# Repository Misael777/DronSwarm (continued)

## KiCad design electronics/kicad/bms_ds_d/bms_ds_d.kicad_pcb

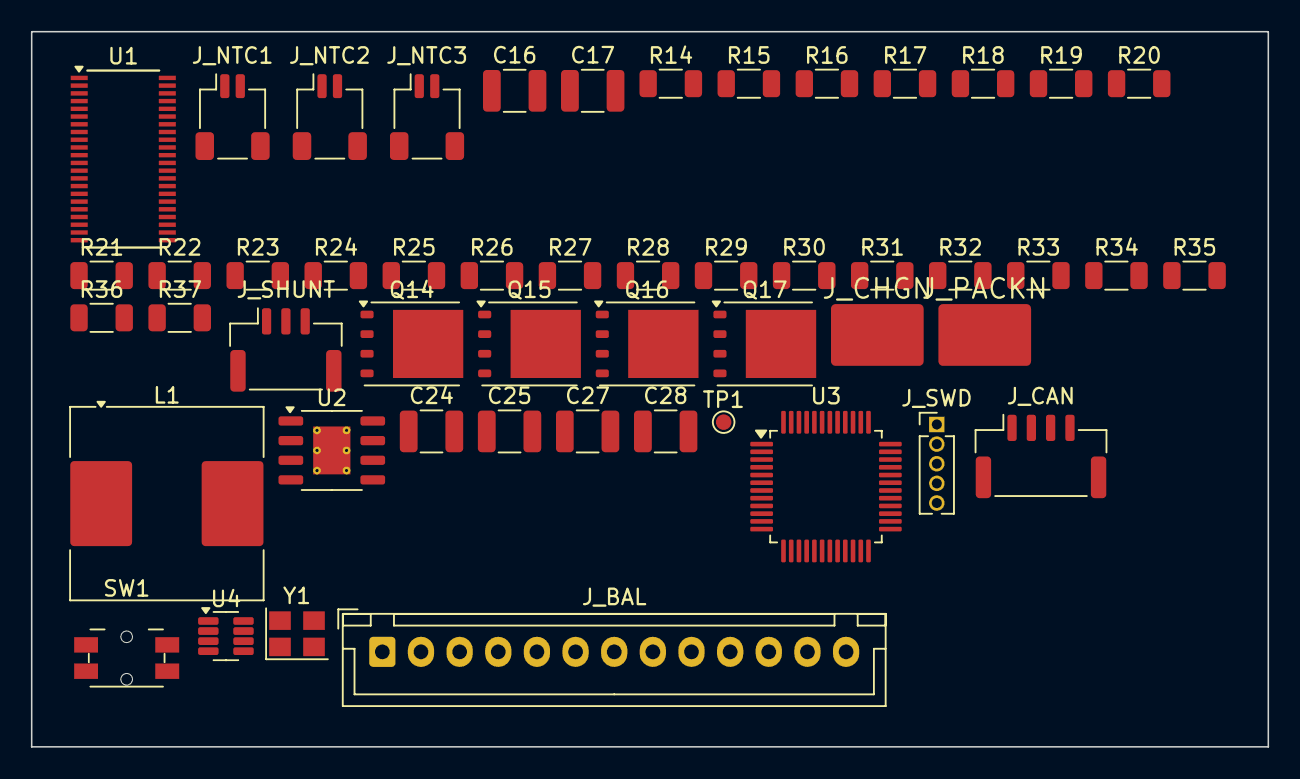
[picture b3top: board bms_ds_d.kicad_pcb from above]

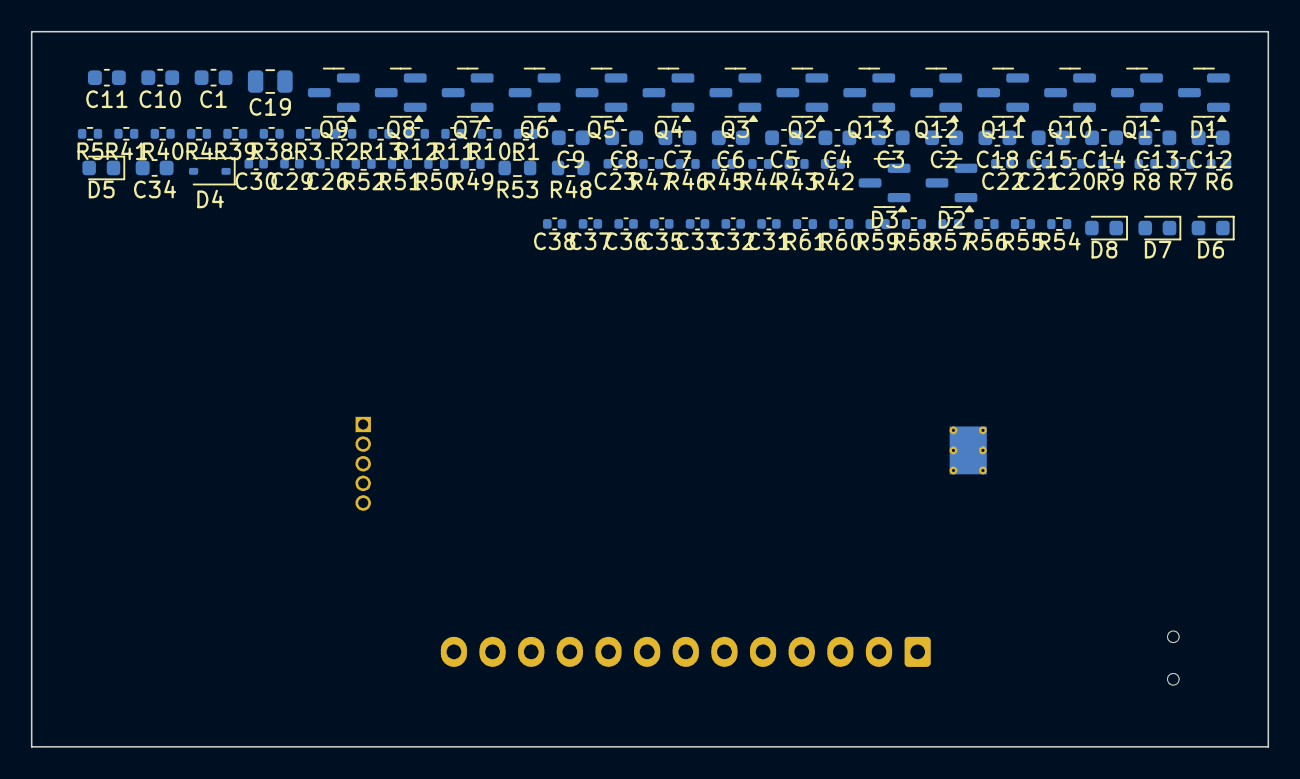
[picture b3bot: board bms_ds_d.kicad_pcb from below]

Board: 4 copper layers, 80.0 x 46.3 mm, 141 parts (90 on the bottom side), 104 nets, no tracks yet.

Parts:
C1, C2, C3, C4, C5, C6, C7, C8, C9, C10, C11, C12, C13, C14, C15: 1u/16V; C_0603_1608Metric
C16, C17: 4.7u/100V; C_1210_3225Metric
C18: 1u/25V; C_0603_1608Metric
C19: 4.7u/10V; C_0805_2012Metric
C20, C21, C22, C23, C31, C32, C33, C35, C38: 100n; C_0402_1005Metric
C24, C25: 2.2u/100V; C_1210_3225Metric
C26: 2.2n/50V; C_0402_1005Metric
C27, C28: 22u/10V; C_1210_3225Metric
C29: 3.3n; C_0402_1005Metric
C30: 150p/C0G; C_0402_1005Metric
C34: 4.7u; C_0603_1608Metric
C36, C37: 10p/C0G; C_0402_1005Metric
D1: BZX84C12; SOT-23
D2, D3: BZX84C15; SOT-23
D4: BAT54; D_SOD-323
D5, D6, D7, D8: verde; LED_0603_1608Metric
J_BAL: Conn_01x13; JST_XH_B13B-XH-A_1x13_P2.50mm_Vertical
J_CAN: Conn_01x04; JST_GH_SM04B-GHS-TB_1x04-1MP_P1.25mm_Horizontal
J_CHGN: Conn_01x01; Pad_Power_6x4mm
J_NTC1, J_NTC2, J_NTC3: Conn_01x02; JST_SH_SM02B-SRSS-TB_1x02-1MP_P1.00mm_Horizontal
J_PACKN: Conn_01x01; Pad_Power_6x4mm
J_SHUNT: Conn_01x03; JST_GH_SM03B-GHS-TB_1x03-1MP_P1.25mm_Horizontal
J_SWD: Conn_01x05; PinHeader_1x05_P1.27mm_Vertical
L1: 47u; L_Coilcraft_MSS1246-XXX
Q1, Q2, Q3, Q4, Q5, Q6, Q7, Q8, Q9, Q10, Q11, Q12: AO3401A; SOT-23
Q13: BSS123; SOT-23
Q14, Q15, Q16, Q17: BSC035N10NS5; TDSON-8-1
R1, R2, R3, R4, R5, R6, R7, R8, R9, R10, R11, R12, R13, R44, R46, R57, R58, R59, R60, R61: 1k; R_0402_1005Metric
R14, R15, R16, R17, R18, R19, R20, R21, R22, R23, R24, R25, R26, R27, R28, R29, R30, R31, R32, R33, R34, R35, R36, R37: 18; R_1206_3216Metric
R38, R39, R40, R42, R43: 100; R_0402_1005Metric
R41, R45, R47, R56: 1M; R_0402_1005Metric
R48: 1M; R_0603_1608Metric
R49: 45.3k; R_0402_1005Metric
R50: 27.4k; R_0402_1005Metric
R51: 174k; R_0402_1005Metric
R52: 100k; R_0402_1005Metric
R53: 140k; R_0603_1608Metric
R54, R55: 4.7k; R_0402_1005Metric
SW1: SW_Push; Panasonic_EVQPUL_EVQPUC
TP1: TestPoint; TestPoint_Pad_D1.0mm
U1: BQ7694003DBT; TSSOP-44_4.4x11.2mm_P0.5mm
U2: LM5164DDA; HSOP-8-1EP_3.9x4.9mm_P1.27mm_EP2.41x3.1mm_ThermalVias
U3: STM32G0B1CBTx; LQFP-48_7x7mm_P0.5mm
U4: TCAN330; SOT-23-8
Y1: 8MHz; Crystal_SMD_3225-4Pin_3.2x2.5mm

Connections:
3V3: C27.1, C28.1, C29.2, C31.1, C32.1, C33.1, C34.1, C38.1, J_SWD.1, L1.2, R51.1, R54.2, R55.2, U3.4, U3.5, U3.6, U4.3
5X_REF: C14.2, C21.2, J_NTC2.2, R38.2, U1.10
10X_REF: C15.2, C22.2, J_NTC3.2, R39.2, U1.15
AFE_ALERT: R56.1, U1.44, U3.44
AFE_BAT: C16.1, C17.1, Q13.3, R40.2, R41.1, U1.20
AFE_BOOT: D4.2, R57.2
BAL1_D: Q1.3, R14.1
BAL1_M: R14.2, R15.1
BAL2_D: Q2.3, R16.1
BAL2_M: R16.2, R17.1
BAL3_D: Q3.3, R18.1
BAL3_M: R18.2, R19.1
BAL4_D: Q4.3, R20.1
BAL4_M: R20.2, R21.1
BAL5_D: Q5.3, R22.1
BAL5_M: R22.2, R23.1
BAL6_D: Q6.3, R24.1
BAL6_M: R24.2, R25.1
BAL7_D: Q7.3, R26.1
BAL7_M: R26.2, R27.1
BAL8_D: Q8.3, R28.1
BAL8_M: R28.2, R29.1
BAL9_D: Q9.3, R30.1
BAL9_M: R30.2, R31.1
BAL10_D: Q10.3, R32.1
BAL10_M: R32.2, R33.1
BAL11_D: Q11.3, R34.1
BAL11_M: R34.2, R35.1
BAL12_D: Q12.3, R36.1
BAL12_M: R36.2, R37.1
BUCK_EN: R48.2, R49.1, U2.3
BUCK_FB: C30.2, R51.2, R52.1, U2.5
BUCK_RA: C29.1, C30.1, R53.2
CAP2: C14.1, U1.11, U1.12, U1.14
CAP3: C15.1, U1.16, U1.17, U1.19
CELL1: J_BAL.2, Q1.2, R2.1, R17.2
CELL2: J_BAL.3, Q2.2, R3.1, R19.2
CELL3: J_BAL.4, Q3.2, R4.1, R21.2
CELL4: J_BAL.5, Q4.2, R5.1, R23.2, R38.1
CELL5: J_BAL.6, Q5.2, R6.1, R25.2
CELL6: J_BAL.7, Q6.2, R7.1, R27.2
CELL7: J_BAL.8, Q7.2, R8.1, R29.2
CELL8: J_BAL.9, Q8.2, R9.1, R31.2, R39.1
CELL9: J_BAL.10, Q9.2, R10.1, R33.2
CELL10: J_BAL.11, Q10.2, R11.1, R35.2
CELL11: J_BAL.12, Q11.2, R12.1, R37.2
CELL12: C24.1, C25.1, J_BAL.13, Q12.2, R13.1, R40.1, R48.1, U2.2
CHG_G: D3.3, Q16.4, Q17.4, R46.2, R47.1
CHG_MID: Q14.5, Q15.5, Q16.5, Q17.5
CHG_N: D3.1, J_CHGN.1, Q16.1, Q16.2, Q16.3, Q17.1, Q17.2, Q17.3, R47.2
DSG_G: D2.3, Q14.4, Q15.4, R44.2, R45.1
GND: C13.2, C16.2, C17.2, C18.2, C19.2, C20.2, C24.2, C25.2, C27.2, C28.2, C31.2, C32.2, C33.2, C34.2, C35.2, C36.2, C37.2, C38.2, D1.1, D5.1, D6.1, D7.1, D8.1, J_BAL.1, J_CAN.4, J_NTC1.2, J_SHUNT.3, J_SWD.5, R1.1, R15.2, R49.2, R50.2, R52.2, R56.2, SW1.2, U1.3, U2.1, U2.9, U3.7, U4.2, U4.5, U4.8, Y1.2, Y1.4
unnamed: C13.1, U1.7
unnamed: C19.1, U1.8
unnamed: R44.1, U1.1
unnamed: R46.1, U1.2
unnamed: R50.1, U2.4
unnamed: C26.1, U2.7
unnamed: TP1.1, U2.6
unnamed: C36.1, U3.8, Y1.1
unnamed: C37.1, U3.9, Y1.3
unnamed: R54.1, U1.5, U3.45
unnamed: R55.1, U1.4, U3.46
unnamed: R57.1, U3.43
unnamed: U3.39, U4.1
unnamed: U3.38, U4.4
unnamed: J_CAN.2, U4.7
unnamed: J_CAN.3, U4.6
unnamed: R58.1, U3.19
unnamed: R59.1, U3.20
unnamed: R60.1, U3.21
unnamed: R61.1, U3.22
unnamed: SW1.1, U3.24
unnamed: J_SWD.2, U3.35
unnamed: J_SWD.3, U3.36
NRST: C35.1, J_SWD.4, U3.10
PACK_N: D2.1, J_PACKN.1, Q14.1, Q14.2, Q14.3, Q15.1, Q15.2, Q15.3, R45.2
REGSRC: C18.1, Q13.2, U1.9
REGSRC_G: D1.3, Q13.1, R41.2
SHUNT_K_N: J_SHUNT.2, R43.1
SHUNT_K_P: J_SHUNT.1, R42.1
SOC_LED1: D5.2, R58.2
SOC_LED2: D6.2, R59.2
SOC_LED3: D7.2, R60.2
SOC_LED4: D8.2, R61.2
SRN: C23.2, R43.2, U1.43
SRP: C23.1, R42.2, U1.42
SW_BUCK: C26.2, L1.1, R53.1, U2.8
TS1: C20.1, D4.1, J_NTC1.1, U1.6
TS2: C21.1, J_NTC2.1, U1.13
TS3: C22.1, J_NTC3.1, U1.18
VC_N0: C1.2, R1.2, U1.41
VC_N1: C1.1, C2.2, Q1.1, R2.2, U1.40
VC_N2: C2.1, C3.2, Q2.1, R3.2, U1.39
VC_N3: C3.1, C4.2, Q3.1, R4.2, U1.37, U1.38
VC_N4: C4.1, C5.2, Q4.1, R5.2, U1.35, U1.36
VC_N5: C5.1, C6.2, Q5.1, R6.2, U1.34
VC_N6: C6.1, C7.2, Q6.1, R7.2, U1.33
VC_N7: C7.1, C8.2, Q7.1, R8.2, U1.31, U1.32
VC_N8: C8.1, C9.2, Q8.1, R9.2, U1.29, U1.30
VC_N9: C9.1, C10.2, Q9.1, R10.2, U1.28
VC_N10: C10.1, C11.2, Q10.1, R11.2, U1.27
VC_N11: C11.1, C12.2, Q11.1, R12.2, U1.25, U1.26
VC_N12: C12.1, Q12.1, R13.2, U1.24

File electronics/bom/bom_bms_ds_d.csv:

Comment,Designator,Footprint,Quantity,Unit price USD (est.)
18,"R14,R15,R16,R17,R18,R19,R20,R21,R22,R23,R24,R25,R26,R27,R28,R29,R30,R31,R32,R33,R34,R35,R36,R37",Resistor_SMD:R_1206_3216Metric,24,0.008
1k,"R1,R2,R3,R4,R5,R6,R7,R8,R9,R10,R11,R12,R13,R44,R46,R57,R58,R59,R60,R61",Resistor_SMD:R_0402_1005Metric,20,0.002
1u/16V,"C1,C2,C3,C4,C5,C6,C7,C8,C9,C10,C11,C12,C13,C14,C15",Capacitor_SMD:C_0603_1608Metric,15,0.008
AO3401A,"Q1,Q2,Q3,Q4,Q5,Q6,Q7,Q8,Q9,Q10,Q11,Q12",Package_TO_SOT_SMD:SOT-23,12,0.03
100n,"C20,C21,C22,C23,C31,C32,C33,C35,C38",Capacitor_SMD:C_0402_1005Metric,9,0.004
100,"R38,R39,R40,R42,R43",Resistor_SMD:R_0402_1005Metric,5,0.002
1M,"R41,R45,R47,R56",Resistor_SMD:R_0402_1005Metric,4,0.002
BSC035N10NS5,"Q14,Q15,Q16,Q17",Package_TO_SOT_SMD:TDSON-8-1,4,1.2
verde,"D5,D6,D7,D8",LED_SMD:LED_0603_1608Metric,4,0.02
Conn_01x02,"J_NTC1,J_NTC2,J_NTC3",Connector_JST:JST_SH_SM02B-SRSS-TB_1x02-1MP_P1.00mm_Horizontal,3,0.12
10p/C0G,"C36,C37",Capacitor_SMD:C_0402_1005Metric,2,0.004
2.2u/100V,"C24,C25",Capacitor_SMD:C_1210_3225Metric,2,0.15
22u/10V,"C27,C28",Capacitor_SMD:C_1210_3225Metric,2,0.1
4.7k,"R54,R55",Resistor_SMD:R_0402_1005Metric,2,0.002
4.7u/100V,"C16,C17",Capacitor_SMD:C_1210_3225Metric,2,0.25
BZX84C15,"D2,D3",Package_TO_SOT_SMD:SOT-23,2,0.02
Conn_01x01,"J_CHGN,J_PACKN",DronSwarm:Pad_Power_6x4mm,2,0.0
100k,R52,Resistor_SMD:R_0402_1005Metric,1,0.002
140k,R53,Resistor_SMD:R_0603_1608Metric,1,0.003
150p/C0G,C30,Capacitor_SMD:C_0402_1005Metric,1,0.004
174k,R51,Resistor_SMD:R_0402_1005Metric,1,0.002
1M,R48,Resistor_SMD:R_0603_1608Metric,1,0.003
1u/25V,C18,Capacitor_SMD:C_0603_1608Metric,1,0.008
2.2n/50V,C26,Capacitor_SMD:C_0402_1005Metric,1,0.004
27.4k,R50,Resistor_SMD:R_0402_1005Metric,1,0.002
3.3n,C29,Capacitor_SMD:C_0402_1005Metric,1,0.004
4.7u,C34,Capacitor_SMD:C_0603_1608Metric,1,0.008
4.7u/10V,C19,Capacitor_SMD:C_0805_2012Metric,1,0.03
45.3k,R49,Resistor_SMD:R_0402_1005Metric,1,0.002
47u,L1,Inductor_SMD:L_Coilcraft_MSS1246-XXX,1,0.45
8MHz,Y1,Crystal:Crystal_SMD_3225-4Pin_3.2x2.5mm,1,0.12
BAT54,D4,Diode_SMD:D_SOD-323,1,0.03
BQ7694003DBT,U1,Package_SO:TSSOP-44_4.4x11.2mm_P0.5mm,1,3.0
BSS123,Q13,Package_TO_SOT_SMD:SOT-23,1,0.02
BZX84C12,D1,Package_TO_SOT_SMD:SOT-23,1,0.02
Conn_01x03,J_SHUNT,Connector_JST:JST_GH_SM03B-GHS-TB_1x03-1MP_P1.25mm_Horizontal,1,0.18
Conn_01x04,J_CAN,Connector_JST:JST_GH_SM04B-GHS-TB_1x04-1MP_P1.25mm_Horizontal,1,0.2
Conn_01x05,J_SWD,Connector_PinHeader_1.27mm:PinHeader_1x05_P1.27mm_Vertical,1,0.05
Conn_01x13,J_BAL,Connector_JST:JST_XH_B13B-XH-A_1x13_P2.50mm_Vertical,1,0.25
LM5164DDA,U2,Package_SO:HSOP-8-1EP_3.9x4.9mm_P1.27mm_EP2.41x3.1mm_ThermalVias,1,1.4
STM32G0B1CBTx,U3,Package_QFP:LQFP-48_7x7mm_P0.5mm,1,2.2
SW_Push,SW1,Button_Switch_SMD:Panasonic_EVQPUL_EVQPUC,1,0.1
TCAN330,U4,Package_TO_SOT_SMD:SOT-23-8,1,0.9
TestPoint,TP1,TestPoint:TestPoint_Pad_D1.0mm,1,0.0

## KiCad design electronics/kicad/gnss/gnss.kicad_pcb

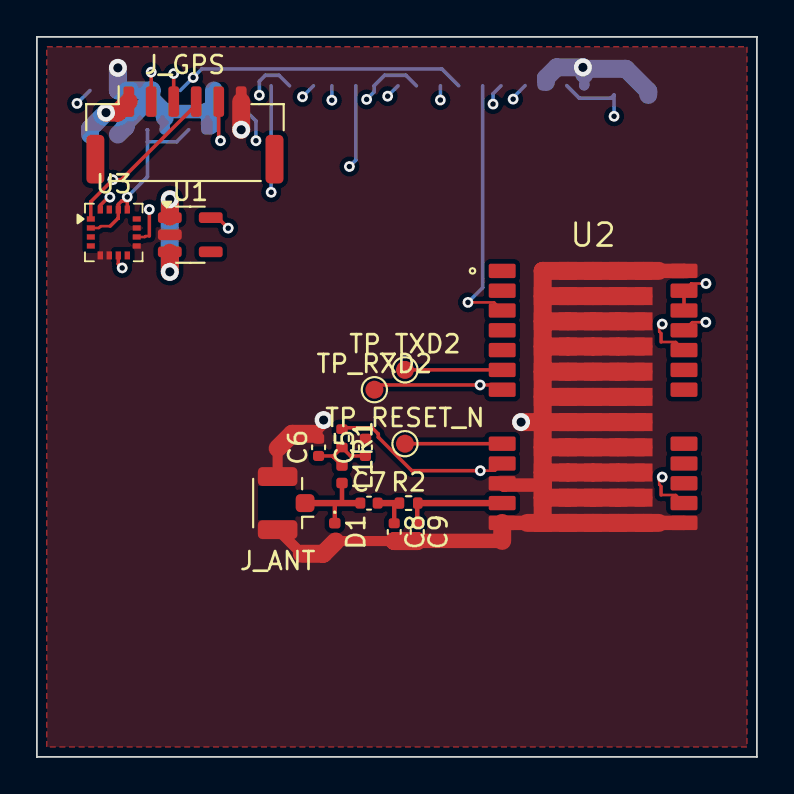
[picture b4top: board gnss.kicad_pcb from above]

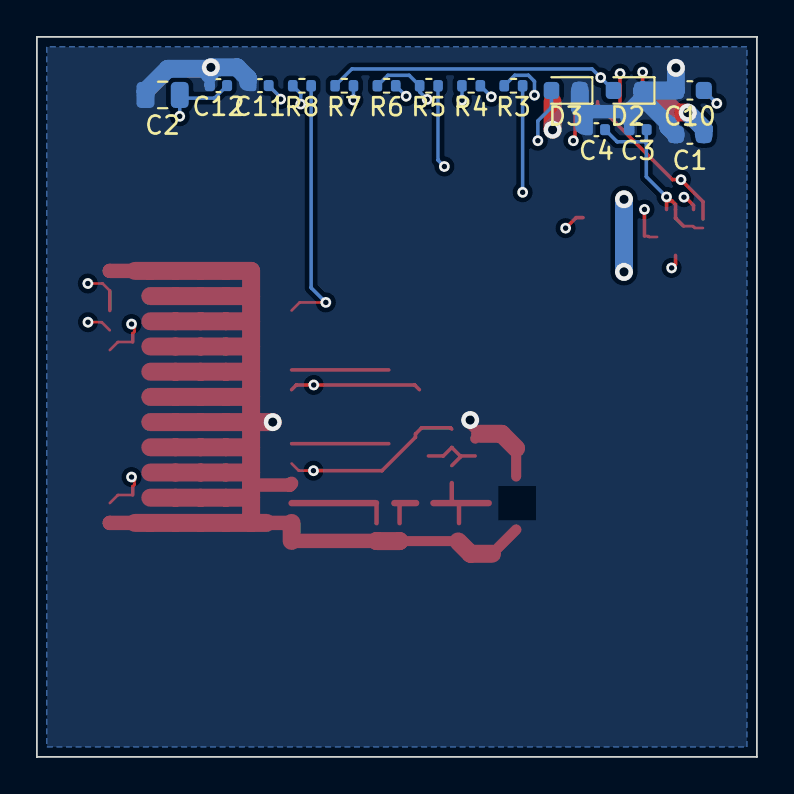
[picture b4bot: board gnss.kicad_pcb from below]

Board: 4 copper layers, 40.0 x 40.0 mm, 32 parts (15 on the bottom side), 23 nets.

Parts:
C1, C10: 1u; C_0603_1608Metric
C2: 10u/10V; C_0805_2012Metric
C3, C6, C11, C12: 100n; C_0402_1005Metric
C4, C5, C7: 100p/C0G; C_0402_1005Metric
C8, C9: DNP; C_0402_1005Metric
D1: ESD0P2RF-02LS; D_0402_1005Metric
D2: verde; LED_0603_1608Metric
D3: azul; LED_0603_1608Metric
J_ANT: Conn_Coaxial; U.FL_Hirose_U.FL-R-SMT-1_Vertical
J_GPS: Conn_01x06; JST_GH_SM06B-GHS-TB_1x06-1MP_P1.25mm_Horizontal
L1: 68n; L_0402_1005Metric
R1: 10; R_0402_1005Metric
R2: 0; R_0402_1005Metric
R3, R4: 22; R_0402_1005Metric
R5, R6: 2.2k; R_0402_1005Metric
R7, R8: 1k; R_0402_1005Metric
TP_RESET_N: TestPoint; TestPoint_Pad_D1.0mm
TP_RXD2: TestPoint; TestPoint_Pad_D1.0mm
TP_TXD2: TestPoint; TestPoint_Pad_D1.0mm
U1: TLV75533PDBV; SOT-23-5
U2: LG290P; Quectel_LG290P_LGA-79_12.2x16mm
U3: IST8310; LGA-16_3x3mm_P0.5mm

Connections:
3V3_GNSS: C2.1, C3.1, C4.1, C12.1, R5.2, R6.2, U1.5, U2.22, U2.23, U3.2, U3.13, U3.14
5V: C1.1, J_GPS.1, U1.1, U1.3
ANT_FEED: C5.1, C6.1, L1.1, R1.2
ANT_LINE: C7.1, D1.1, J_ANT.1, L1.2
GND: C1.2, C2.2, C3.2, C4.2, C5.2, C6.2, C8.2, C9.2, C10.2, C11.2, C12.2, D1.2, D2.1, D3.1, J_ANT.2, J_GPS.6, U1.2, U2.10, U2.12, U2.13, U2.24, U2.25, U2.26, U2.27, U2.28, U2.29, U2.30, U2.31, U2.32, U2.33, U2.34, U2.35, U2.36, U2.37, U2.38, U2.39, U2.40, U2.41, U2.42, U2.43, U2.44, U2.45, U2.46, U2.47, U2.48, U2.49, U2.50, U2.51, U2.52, U2.53, U2.54, U2.55, U2.56, U2.57, U2.58, U2.59, U2.60, U2.61, U2.62, U2.63, U2.64, U2.65, U2.66, U2.67, U2.68, U2.69, U2.70, U2.71, U2.72, U2.73, U2.74, U2.75, U2.76, U2.77, U2.78, U2.79, U3.5, U3.6, U3.9, U3.11
GPS_RX: J_GPS.2, R4.1
GPS_TX: J_GPS.3, R3.2
I2C_SCL: J_GPS.4, R5.1, U3.1
I2C_SDA: J_GPS.5, R6.1, U3.16
LED_1PPS: D3.2, R8.2
LED_RTK_STAT: D2.2, R7.2
unnamed: R3.1, U2.20
unnamed: R4.2, U2.21
unnamed: C10.1, U3.10
unnamed: C11.1, U3.7
unnamed: R7.1, U2.14
unnamed: R8.1, U2.3
unnamed: TP_TXD2.1, U2.6
unnamed: TP_RXD2.1, U2.7
unnamed: TP_RESET_N.1, U2.8
RF_IN: C9.1, R2.2, U2.11
RF_PI: C7.2, C8.1, R2.1
VDD_RF: R1.1, U2.9

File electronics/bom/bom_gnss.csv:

Comment,Designator,Footprint,Quantity,Unit price USD (est.)
100n,"C3,C6,C11,C12",Capacitor_SMD:C_0402_1005Metric,4,0.004
100p/C0G,"C4,C5,C7",Capacitor_SMD:C_0402_1005Metric,3,0.004
TestPoint,"TP_RESET_N,TP_RXD2,TP_TXD2",TestPoint:TestPoint_Pad_D1.0mm,3,0.0
1k,"R7,R8",Resistor_SMD:R_0402_1005Metric,2,0.002
1u,"C1,C10",Capacitor_SMD:C_0603_1608Metric,2,0.008
2.2k,"R5,R6",Resistor_SMD:R_0402_1005Metric,2,0.002
22,"R3,R4",Resistor_SMD:R_0402_1005Metric,2,0.002
DNP,"C8,C9",Capacitor_SMD:C_0402_1005Metric,2,0.004
0,R2,Resistor_SMD:R_0402_1005Metric,1,0.002
10,R1,Resistor_SMD:R_0402_1005Metric,1,0.002
10u/10V,C2,Capacitor_SMD:C_0805_2012Metric,1,0.03
68n,L1,Inductor_SMD:L_0402_1005Metric,1,0.02
Conn_01x06,J_GPS,Connector_JST:JST_GH_SM06B-GHS-TB_1x06-1MP_P1.25mm_Horizontal,1,0.24
Conn_Coaxial,J_ANT,Connector_Coaxial:U.FL_Hirose_U.FL-R-SMT-1_Vertical,1,0.2
ESD0P2RF-02LS,D1,Diode_SMD:D_0402_1005Metric,1,0.1
IST8310,U3,Package_LGA:LGA-16_3x3mm_P0.5mm,1,0.8
LG290P,U2,DronSwarm:Quectel_LG290P_LGA-79_12.2x16mm,1,72.0
TLV75533PDBV,U1,Package_TO_SOT_SMD:SOT-23-5,1,0.12
azul,D3,LED_SMD:LED_0603_1608Metric,1,0.02
verde,D2,LED_SMD:LED_0603_1608Metric,1,0.02

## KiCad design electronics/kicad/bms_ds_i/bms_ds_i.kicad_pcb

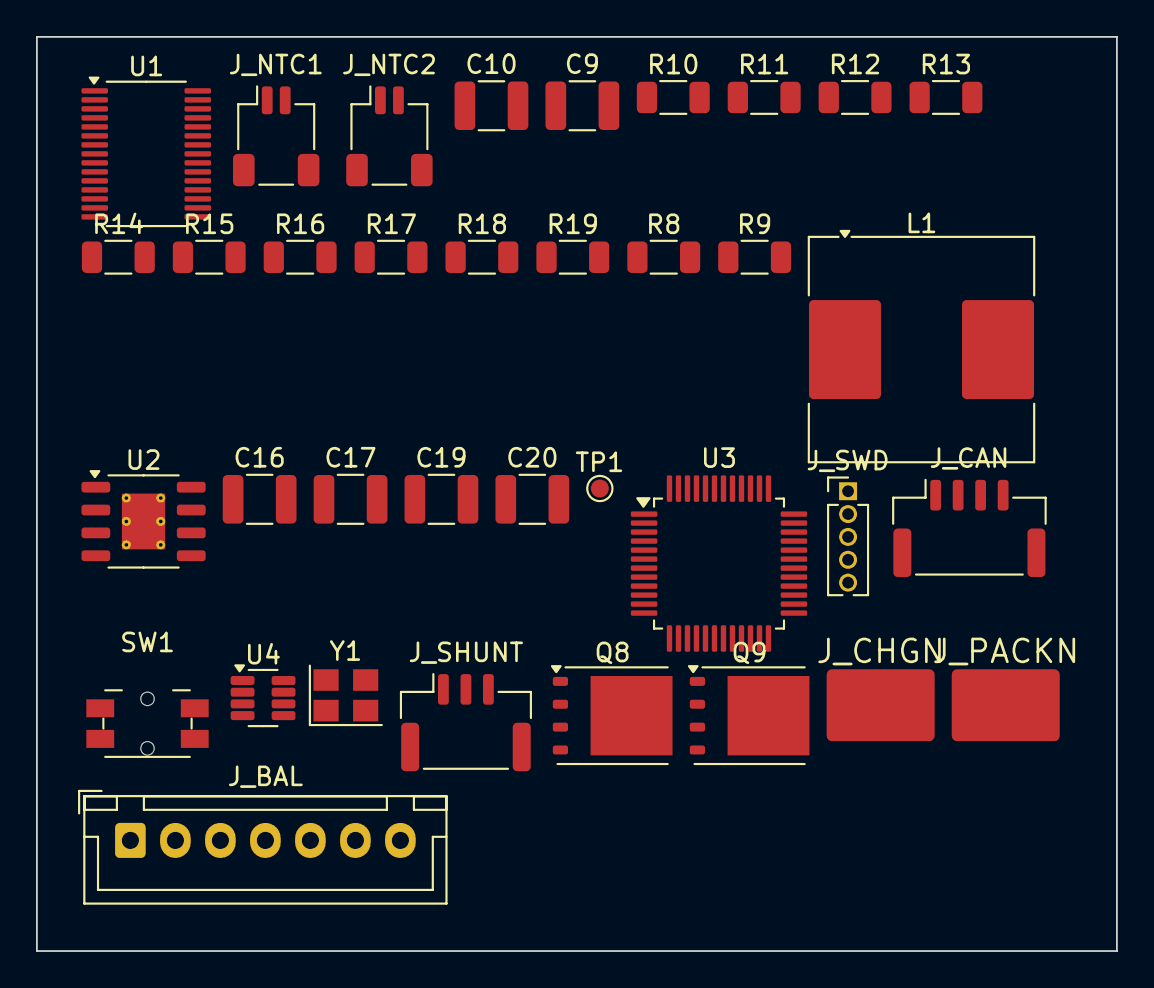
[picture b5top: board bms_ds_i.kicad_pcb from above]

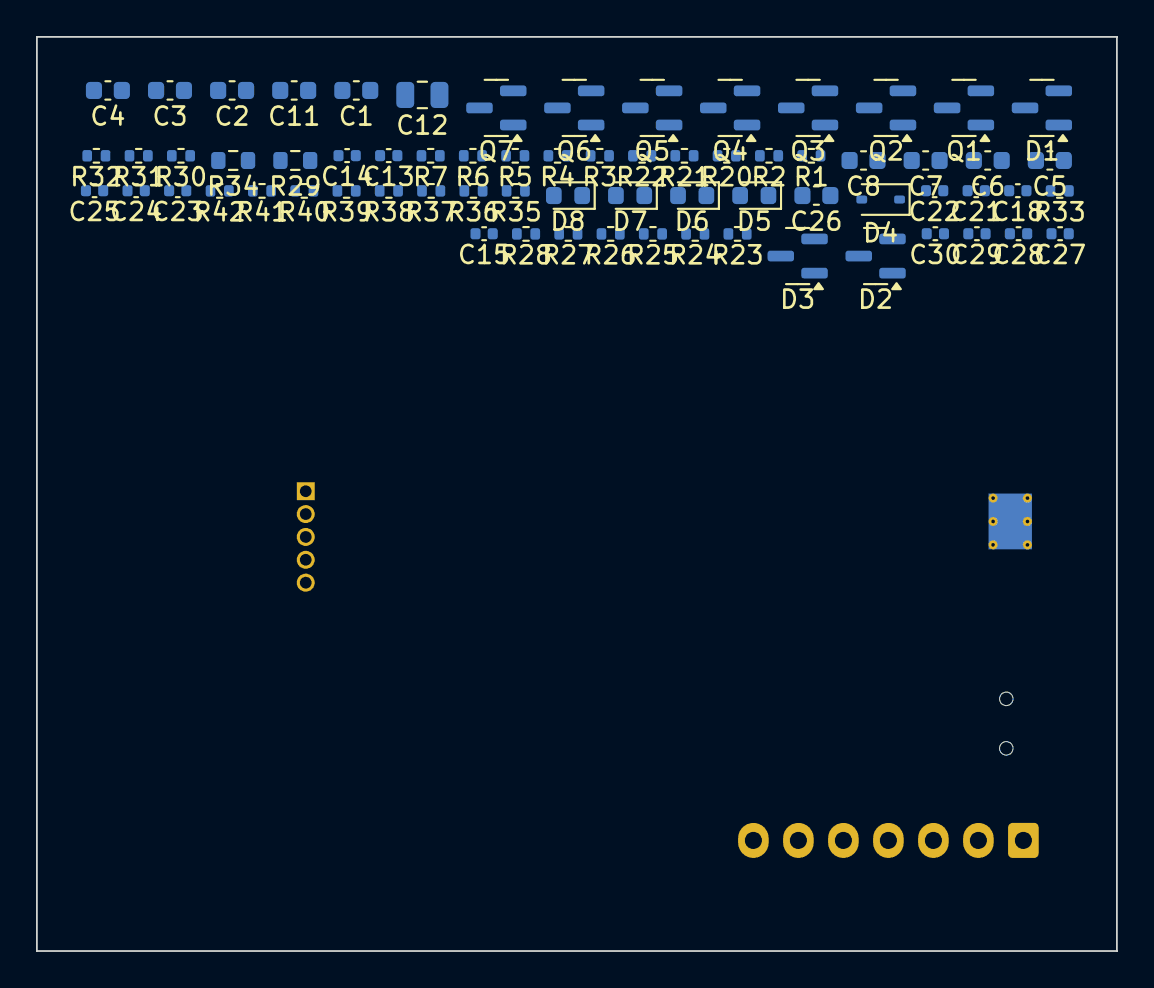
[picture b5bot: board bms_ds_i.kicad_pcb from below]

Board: 4 copper layers, 60.0 x 50.8 mm, 105 parts (69 on the bottom side), 77 nets, no tracks yet.

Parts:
C1, C2, C3, C4, C5, C6, C7, C8: 1u/16V; C_0603_1608Metric
C9, C10: 4.7u/100V; C_1210_3225Metric
C11: 1u/25V; C_0603_1608Metric
C12: 4.7u/10V; C_0805_2012Metric
C13, C14, C15, C23, C24, C25, C27, C30: 100n; C_0402_1005Metric
C16, C17: 2.2u/100V; C_1210_3225Metric
C18: 2.2n/50V; C_0402_1005Metric
C19, C20: 22u/10V; C_1210_3225Metric
C21: 3.3n; C_0402_1005Metric
C22: 150p/C0G; C_0402_1005Metric
C26: 4.7u; C_0603_1608Metric
C28, C29: 10p/C0G; C_0402_1005Metric
D1: BZX84C12; SOT-23
D2, D3: BZX84C15; SOT-23
D4: BAT54; D_SOD-323
D5, D6, D7, D8: verde; LED_0603_1608Metric
J_BAL: Conn_01x07; JST_XH_B7B-XH-A_1x07_P2.50mm_Vertical
J_CAN: Conn_01x04; JST_GH_SM04B-GHS-TB_1x04-1MP_P1.25mm_Horizontal
J_CHGN: Conn_01x01; Pad_Power_6x4mm
J_NTC1, J_NTC2: Conn_01x02; JST_SH_SM02B-SRSS-TB_1x02-1MP_P1.00mm_Horizontal
J_PACKN: Conn_01x01; Pad_Power_6x4mm
J_SHUNT: Conn_01x03; JST_GH_SM03B-GHS-TB_1x03-1MP_P1.25mm_Horizontal
J_SWD: Conn_01x05; PinHeader_1x05_P1.27mm_Vertical
L1: 47u; L_Coilcraft_MSS1246-XXX
Q1, Q2, Q3, Q4, Q5, Q6: AO3401A; SOT-23
Q7: BSS123; SOT-23
Q8, Q9: BSC035N10NS5; TDSON-8-1
R1, R2, R3, R4, R5, R6, R7, R25, R27, R38, R39, R40, R41, R42: 1k; R_0402_1005Metric
R8, R9, R10, R11, R12, R13, R14, R15, R16, R17, R18, R19: 18; R_1206_3216Metric
R20, R21, R23, R24: 100; R_0402_1005Metric
R22, R26, R28, R37: 1M; R_0402_1005Metric
R29: 1M; R_0603_1608Metric
R30: 94.2k; R_0402_1005Metric
R31: 27.4k; R_0402_1005Metric
R32: 174k; R_0402_1005Metric
R33: 100k; R_0402_1005Metric
R34: 140k; R_0603_1608Metric
R35, R36: 4.7k; R_0402_1005Metric
SW1: SW_Push; Panasonic_EVQPUL_EVQPUC
TP1: TestPoint; TestPoint_Pad_D1.0mm
U1: BQ7693003DBT; TSSOP-30_4.4x7.8mm_P0.5mm
U2: LM5164DDA; HSOP-8-1EP_3.9x4.9mm_P1.27mm_EP2.41x3.1mm_ThermalVias
U3: STM32G0B1CBTx; LQFP-48_7x7mm_P0.5mm
U4: TCAN330; SOT-23-8
Y1: 8MHz; Crystal_SMD_3225-4Pin_3.2x2.5mm

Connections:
3V3: C19.1, C20.1, C21.2, C23.1, C24.1, C25.1, C26.1, C30.1, J_SWD.1, L1.2, R32.1, R35.2, R36.2, U3.4, U3.5, U3.6, U4.3
5X_REF: C8.2, C14.2, J_NTC2.2, R20.2, U1.10
AFE_ALERT: R37.1, U1.30, U3.44
AFE_BAT: C9.1, C10.1, Q7.3, R21.2, R22.1, U1.15
AFE_BOOT: D4.2, R38.2
BAL1_D: Q1.3, R8.1
BAL1_M: R8.2, R9.1
BAL2_D: Q2.3, R10.1
BAL2_M: R10.2, R11.1
BAL3_D: Q3.3, R12.1
BAL3_M: R12.2, R13.1
BAL4_D: Q4.3, R14.1
BAL4_M: R14.2, R15.1
BAL5_D: Q5.3, R16.1
BAL5_M: R16.2, R17.1
BAL6_D: Q6.3, R18.1
BAL6_M: R18.2, R19.1
BUCK_EN: R29.2, R30.1, U2.3
BUCK_FB: C22.2, R32.2, R33.1, U2.5
BUCK_RA: C21.1, C22.1, R34.2
CAP2: C8.1, U1.11, U1.12, U1.14
CELL1: J_BAL.2, Q1.2, R2.1, R11.2
CELL2: J_BAL.3, Q2.2, R3.1, R13.2
CELL3: J_BAL.4, Q3.2, R4.1, R15.2, R20.1
CELL4: J_BAL.5, Q4.2, R5.1, R17.2
CELL5: J_BAL.6, Q5.2, R6.1, R19.2
CELL6: C16.1, C17.1, J_BAL.7, Q6.2, R7.1, R21.1, R29.1, U2.2
CHG_G: D3.3, Q9.4, R27.2, R28.1
CHG_MID: Q8.5, Q9.5
CHG_N: D3.1, J_CHGN.1, Q9.1, Q9.2, Q9.3, R28.2
DSG_G: D2.3, Q8.4, R25.2, R26.1
GND: C7.2, C9.2, C10.2, C11.2, C12.2, C13.2, C16.2, C17.2, C19.2, C20.2, C23.2, C24.2, C25.2, C26.2, C27.2, C28.2, C29.2, C30.2, D1.1, D5.1, D6.1, D7.1, D8.1, J_BAL.1, J_CAN.4, J_NTC1.2, J_SHUNT.3, J_SWD.5, R1.1, R9.2, R30.2, R31.2, R33.2, R37.2, SW1.2, U1.3, U2.1, U2.9, U3.7, U4.2, U4.5, U4.8, Y1.2, Y1.4
unnamed: C7.1, U1.7
unnamed: C12.1, U1.8
unnamed: R25.1, U1.1
unnamed: R27.1, U1.2
unnamed: R31.1, U2.4
unnamed: C18.1, U2.7
unnamed: TP1.1, U2.6
unnamed: C28.1, U3.8, Y1.1
unnamed: C29.1, U3.9, Y1.3
unnamed: R35.1, U1.5, U3.45
unnamed: R36.1, U1.4, U3.46
unnamed: R38.1, U3.43
unnamed: U3.39, U4.1
unnamed: U3.38, U4.4
unnamed: J_CAN.2, U4.7
unnamed: J_CAN.3, U4.6
unnamed: R39.1, U3.19
unnamed: R40.1, U3.20
unnamed: R41.1, U3.21
unnamed: R42.1, U3.22
unnamed: SW1.1, U3.24
unnamed: J_SWD.2, U3.35
unnamed: J_SWD.3, U3.36
NRST: C27.1, J_SWD.4, U3.10
PACK_N: D2.1, J_PACKN.1, Q8.1, Q8.2, Q8.3, R26.2
REGSRC: C11.1, Q7.2, U1.9
REGSRC_G: D1.3, Q7.1, R22.2
SHUNT_K_N: J_SHUNT.2, R24.1
SHUNT_K_P: J_SHUNT.1, R23.1
SOC_LED1: D5.2, R39.2
SOC_LED2: D6.2, R40.2
SOC_LED3: D7.2, R41.2
SOC_LED4: D8.2, R42.2
SRN: C15.2, R24.2, U1.29
SRP: C15.1, R23.2, U1.28
SW_BUCK: C18.2, L1.1, R34.1, U2.8
TS1: C13.1, D4.1, J_NTC1.1, U1.6
TS2: C14.1, J_NTC2.1, U1.13
VC_N0: C1.2, R1.2, U1.27
VC_N1: C1.1, C2.2, Q1.1, R2.2, U1.26
VC_N2: C2.1, C3.2, Q2.1, R3.2, U1.23, U1.24, U1.25
VC_N3: C3.1, C4.2, Q3.1, R4.2, U1.21, U1.22
VC_N4: C4.1, C5.2, Q4.1, R5.2, U1.20
VC_N5: C5.1, C6.2, Q5.1, R6.2, U1.17, U1.18, U1.19
VC_N6: C6.1, Q6.1, R7.2, U1.16

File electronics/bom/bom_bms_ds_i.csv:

Comment,Designator,Footprint,Quantity,Unit price USD (est.)
1k,"R1,R2,R3,R4,R5,R6,R7,R25,R27,R38,R39,R40,R41,R42",Resistor_SMD:R_0402_1005Metric,14,0.002
18,"R8,R9,R10,R11,R12,R13,R14,R15,R16,R17,R18,R19",Resistor_SMD:R_1206_3216Metric,12,0.008
100n,"C13,C14,C15,C23,C24,C25,C27,C30",Capacitor_SMD:C_0402_1005Metric,8,0.004
1u/16V,"C1,C2,C3,C4,C5,C6,C7,C8",Capacitor_SMD:C_0603_1608Metric,8,0.008
AO3401A,"Q1,Q2,Q3,Q4,Q5,Q6",Package_TO_SOT_SMD:SOT-23,6,0.03
100,"R20,R21,R23,R24",Resistor_SMD:R_0402_1005Metric,4,0.002
1M,"R22,R26,R28,R37",Resistor_SMD:R_0402_1005Metric,4,0.002
verde,"D5,D6,D7,D8",LED_SMD:LED_0603_1608Metric,4,0.02
10p/C0G,"C28,C29",Capacitor_SMD:C_0402_1005Metric,2,0.004
2.2u/100V,"C16,C17",Capacitor_SMD:C_1210_3225Metric,2,0.15
22u/10V,"C19,C20",Capacitor_SMD:C_1210_3225Metric,2,0.1
4.7k,"R35,R36",Resistor_SMD:R_0402_1005Metric,2,0.002
4.7u/100V,"C9,C10",Capacitor_SMD:C_1210_3225Metric,2,0.25
BSC035N10NS5,"Q8,Q9",Package_TO_SOT_SMD:TDSON-8-1,2,1.2
BZX84C15,"D2,D3",Package_TO_SOT_SMD:SOT-23,2,0.02
Conn_01x01,"J_CHGN,J_PACKN",DronSwarm:Pad_Power_6x4mm,2,0.0
Conn_01x02,"J_NTC1,J_NTC2",Connector_JST:JST_SH_SM02B-SRSS-TB_1x02-1MP_P1.00mm_Horizontal,2,0.12
100k,R33,Resistor_SMD:R_0402_1005Metric,1,0.002
140k,R34,Resistor_SMD:R_0603_1608Metric,1,0.003
150p/C0G,C22,Capacitor_SMD:C_0402_1005Metric,1,0.004
174k,R32,Resistor_SMD:R_0402_1005Metric,1,0.002
1M,R29,Resistor_SMD:R_0603_1608Metric,1,0.003
1u/25V,C11,Capacitor_SMD:C_0603_1608Metric,1,0.008
2.2n/50V,C18,Capacitor_SMD:C_0402_1005Metric,1,0.004
27.4k,R31,Resistor_SMD:R_0402_1005Metric,1,0.002
3.3n,C21,Capacitor_SMD:C_0402_1005Metric,1,0.004
4.7u,C26,Capacitor_SMD:C_0603_1608Metric,1,0.008
4.7u/10V,C12,Capacitor_SMD:C_0805_2012Metric,1,0.03
47u,L1,Inductor_SMD:L_Coilcraft_MSS1246-XXX,1,0.45
8MHz,Y1,Crystal:Crystal_SMD_3225-4Pin_3.2x2.5mm,1,0.12
94.2k,R30,Resistor_SMD:R_0402_1005Metric,1,0.002
BAT54,D4,Diode_SMD:D_SOD-323,1,0.03
BQ7693003DBT,U1,Package_SO:TSSOP-30_4.4x7.8mm_P0.5mm,1,2.2
BSS123,Q7,Package_TO_SOT_SMD:SOT-23,1,0.02
BZX84C12,D1,Package_TO_SOT_SMD:SOT-23,1,0.02
Conn_01x03,J_SHUNT,Connector_JST:JST_GH_SM03B-GHS-TB_1x03-1MP_P1.25mm_Horizontal,1,0.18
Conn_01x04,J_CAN,Connector_JST:JST_GH_SM04B-GHS-TB_1x04-1MP_P1.25mm_Horizontal,1,0.2
Conn_01x05,J_SWD,Connector_PinHeader_1.27mm:PinHeader_1x05_P1.27mm_Vertical,1,0.05
Conn_01x07,J_BAL,Connector_JST:JST_XH_B7B-XH-A_1x07_P2.50mm_Vertical,1,0.25
LM5164DDA,U2,Package_SO:HSOP-8-1EP_3.9x4.9mm_P1.27mm_EP2.41x3.1mm_ThermalVias,1,1.4
STM32G0B1CBTx,U3,Package_QFP:LQFP-48_7x7mm_P0.5mm,1,2.2
SW_Push,SW1,Button_Switch_SMD:Panasonic_EVQPUL_EVQPUC,1,0.1
TCAN330,U4,Package_TO_SOT_SMD:SOT-23-8,1,0.9
TestPoint,TP1,TestPoint:TestPoint_Pad_D1.0mm,1,0.0

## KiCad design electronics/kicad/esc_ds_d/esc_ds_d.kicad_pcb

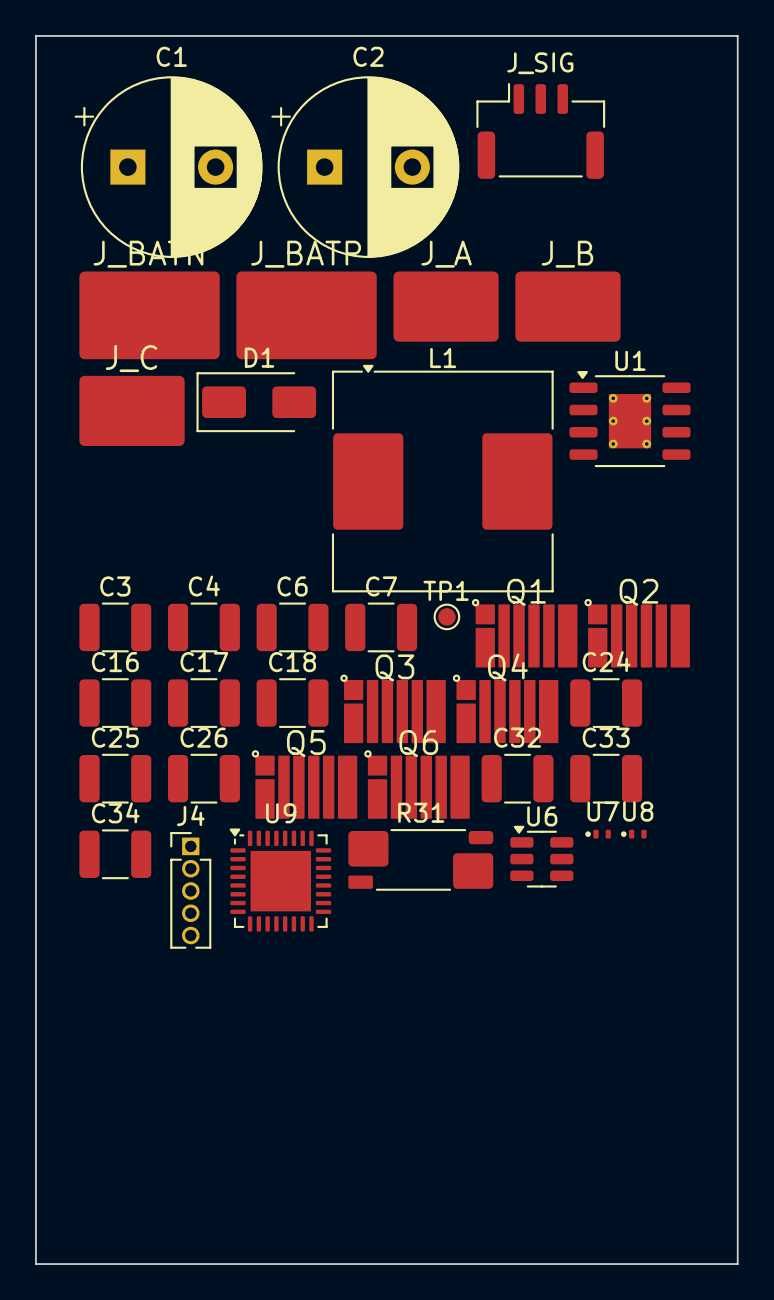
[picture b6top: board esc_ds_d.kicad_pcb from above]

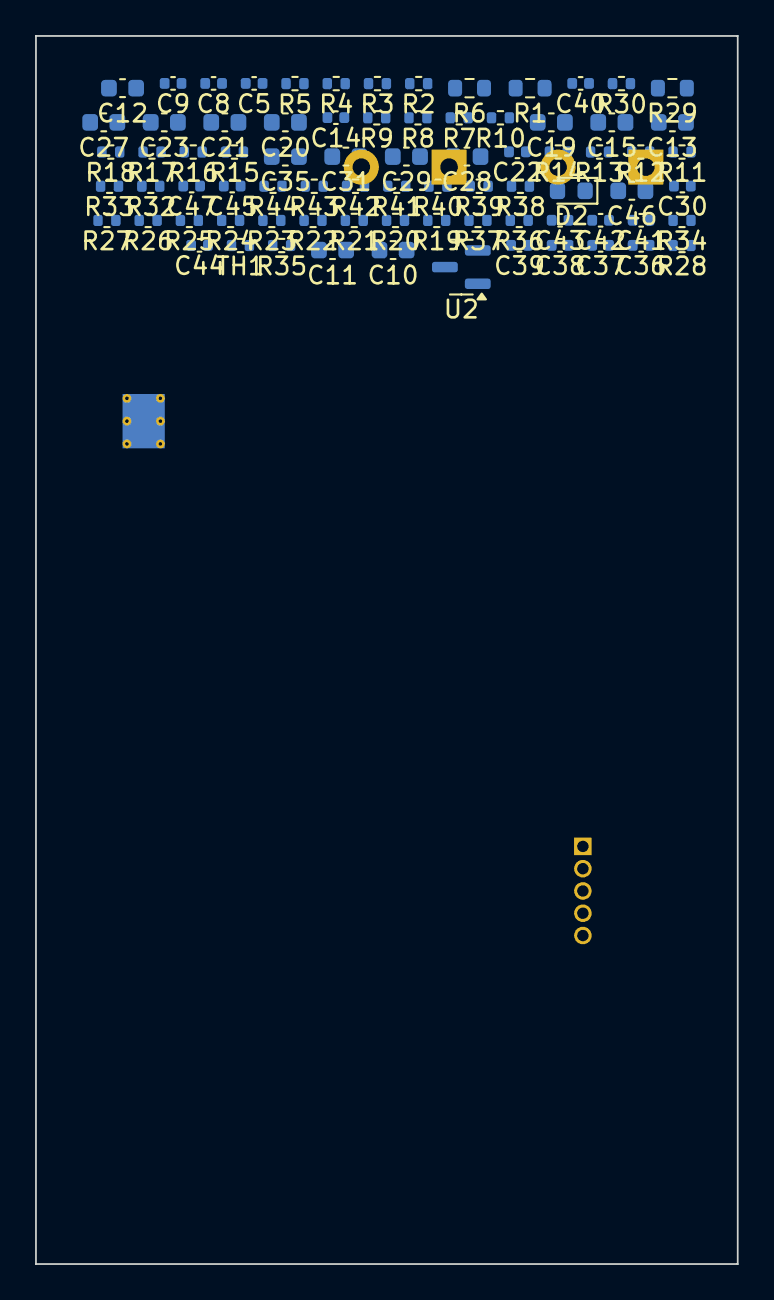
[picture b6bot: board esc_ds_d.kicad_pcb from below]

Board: 4 copper layers, 40.0 x 70.0 mm, 115 parts (78 on the bottom side), 51 nets, no tracks yet.

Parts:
C1, C2: 470u/63V; CP_Radial_D10.0mm_P5.00mm
C3, C4, C16, C17, C18, C24, C25, C26, C32, C33, C34: 2.2u/100V; C_1210_3225Metric
C5: 2.2n/50V; C_0402_1005Metric
C6, C7: 22u/25V; C_1210_3225Metric
C8, C39: 3.3n; C_0402_1005Metric
C9: 56p/C0G; C_0402_1005Metric
C10, C11, C12, C13, C20, C21, C28, C29: 1u; C_0603_1608Metric
C14, C22, C30, C40, C41, C42, C43, C44, C45, C47: 100n; C_0402_1005Metric
C15, C23, C31: 100n; C_0603_1608Metric
C19, C27, C35: 100n/100V; C_0603_1608Metric
C36, C37, C38: 1n; C_0402_1005Metric
C46: 4.7u; C_0603_1608Metric
D1: SMAJ58A; D_SMA
D2: verde; LED_0603_1608Metric
J4: Conn_01x05; PinHeader_1x05_P1.27mm_Vertical
J_A: Conn_01x01; Pad_Power_6x4mm
J_B: Conn_01x01; Pad_Power_6x4mm
J_BATN: Conn_01x01; Pad_Power_8x5mm
J_BATP: Conn_01x01; Pad_Power_8x5mm
J_C: Conn_01x01; Pad_Power_6x4mm
J_SIG: Conn_01x03; JST_GH_SM03B-GHS-TB_1x03-1MP_P1.25mm_Horizontal
L1: 68u; L_Coilcraft_MSS1246-XXX
Q1, Q2, Q3, Q4, Q5, Q6: EPC2302; EPC2302_QFN-3x5mm
R1: 1M; R_0603_1608Metric
R2, R19, R21, R22, R24, R25, R27: 47k; R_0402_1005Metric
R3: 100k; R_0402_1005Metric
R4: 453k; R_0402_1005Metric
R5: 49.9k; R_0402_1005Metric
R6: 453k; R_0603_1608Metric
R7, R8, R11, R12, R15, R16: 2.2; R_0402_1005Metric
R9, R10, R13, R14, R17, R18, R35, R38, R39, R40, R41, R42, R43: 10k; R_0402_1005Metric
R20, R23, R26: 2.7k; R_0402_1005Metric
R28: 910; R_0402_1005Metric
R29: 100k; R_0603_1608Metric
R30: 5.1k; R_0402_1005Metric
R31: 0.5m/3W; R_Shunt_Vishay_WSK2512_6332Metric_T1.19mm
R32, R33: 10; R_0402_1005Metric
R34, R44: 1k; R_0402_1005Metric
R36, R37: 100; R_0402_1005Metric
TH1: 10k B3950; R_0402_1005Metric
TP1: TestPoint; TestPoint_Pad_D1.0mm
U1: LM5164DDA; HSOP-8-1EP_3.9x4.9mm_P1.27mm_EP2.41x3.1mm_ThermalVias
U2: MCP1703Ax-330xxTT; SOT-23
U6: INA181A3; SOT-23-6
U7, U8: TPD1E05U06DPY; Texas_DPY0002A_0.6x1mm_P0.65mm
U9: STM32G071KBUxN; QFN-32-1EP_5x5mm_P0.5mm_EP3.45x3.45mm

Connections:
3V3: C11.1, C42.1, C45.1, C46.1, J4.1, R35.1, U2.2, U6.6, U9.4
12V: C6.1, C7.1, C8.2, C10.1, C12.1, C20.1, C28.1, L1.2, R4.1, U2.3
BAT_N: J_BATN.1, R31.4
BEMF_A: C36.1, R19.2, R20.1, U9.31
BEMF_B: C37.1, R22.2, R23.1, U9.9
BEMF_C: C38.1, R25.2, R26.1, U9.7
BEMF_N: C39.1, R21.2, R24.2, R27.2, R28.1, U9.8, U9.10
BUCK_EN: R1.2, R2.1, U1.3
BUCK_FB: C9.2, R4.2, R5.1, U1.5
BUCK_RA: C8.1, C9.1, R6.2
DSHOT: R36.2, U9.13
DSHOT_IN: J_SIG.1, R36.1, U7.1
GA_HI: Q1.1, R7.2, R9.1
GA_LO: Q2.1, R8.2, R10.1
GB_HI: Q3.1, R11.2, R13.1
GB_LO: Q4.1, R12.2, R14.1
GC_HI: Q5.1, R15.2, R17.1
GC_LO: Q6.1, R16.2, R18.1
GND: C1.2, C2.2, C3.2, C4.2, C6.2, C7.2, C10.2, C11.2, C12.2, C13.2, C14.2, C16.2, C17.2, C18.2, C19.2, C20.2, C21.2, C22.2, C24.2, C25.2, C26.2, C27.2, C28.2, C29.2, C30.2, C32.2, C33.2, C34.2, C35.2, C36.2, C37.2, C38.2, C39.2, C40.2, C42.2, C43.2, C44.2, C45.2, C46.2, C47.2, D1.2, D2.1, J4.5, J_SIG.3, Q2.2, Q2.4, Q2.6, Q4.2, Q4.4, Q4.6, Q6.2, Q6.4, Q6.6, R2.2, R3.2, R5.2, R10.2, R14.2, R18.2, R20.2, R23.2, R26.2, R28.2, R30.2, R31.1, R38.2, R39.2, R40.2, R41.2, R42.2, R43.2, TH1.2, U1.1, U1.9, U2.1, U6.2, U6.5, U7.2, U8.2, U9.5, U9.33
ISENSE: C43.1, R34.2, U9.11
ISENSE_N: C41.2, R33.2, U6.4
ISENSE_P: C41.1, R32.2, U6.3
LED_A: D2.2, R44.2
unnamed: R3.1, U1.4
unnamed: C5.1, U1.7
unnamed: TP1.1, U1.6
unnamed: R31.2, R32.1
unnamed: R31.3, R33.1
unnamed: R34.1, U6.1
unnamed: R44.1, U9.32
unnamed: J4.2, U9.24
unnamed: J4.3, U9.25
NRST: C47.1, J4.4, U9.6
PHASE_A: C15.2, J_A.1, Q1.2, Q1.4, Q1.6, Q2.3, Q2.5, Q2.7, R9.2, R19.1, R21.1
PHASE_B: C23.2, J_B.1, Q3.2, Q3.4, Q3.6, Q4.3, Q4.5, Q4.7, R13.2, R22.1, R24.1
PHASE_C: C31.2, J_C.1, Q5.2, Q5.4, Q5.6, Q6.3, Q6.5, Q6.7, R17.2, R25.1, R27.1
PWM_A_HI: R38.1, U9.21
PWM_A_LO: R39.1, U9.17
PWM_B_HI: R40.1, U9.19
PWM_B_LO: R41.1, U9.15
PWM_C_HI: R42.1, U9.18
PWM_C_LO: R43.1, U9.14
SW_BUCK: C5.2, L1.1, R6.1, U1.8
TEMP_SENSE: C44.1, R35.2, TH1.1, U9.16
TLM: R37.2, U9.30
TLM_OUT: J_SIG.2, R37.1, U8.1
VBUS: C1.1, C2.1, C3.1, C4.1, C16.1, C17.1, C18.1, C19.1, C24.1, C25.1, C26.1, C27.1, C32.1, C33.1, C34.1, C35.1, D1.1, J_BATP.1, Q1.3, Q1.5, Q1.7, Q3.3, Q3.5, Q3.7, Q5.3, Q5.5, Q5.7, R1.1, R29.1, U1.2
VBUS_SENSE: C40.1, R29.2, R30.1, U9.12
VDD5_A: C13.1, C14.1
VDD5_B: C21.1, C22.1
VDD5_C: C29.1, C30.1

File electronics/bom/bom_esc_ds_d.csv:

Comment,Designator,Footprint,Quantity,Unit price USD (est.)
10k,"R9,R10,R13,R14,R17,R18,R35,R38,R39,R40,R41,R42,R43",Resistor_SMD:R_0402_1005Metric,13,0.002
2.2u/100V,"C3,C4,C16,C17,C18,C24,C25,C26,C32,C33,C34",Capacitor_SMD:C_1210_3225Metric,11,0.15
100n,"C14,C22,C30,C40,C41,C42,C43,C44,C45,C47",Capacitor_SMD:C_0402_1005Metric,10,0.004
1u,"C10,C11,C12,C13,C20,C21,C28,C29",Capacitor_SMD:C_0603_1608Metric,8,0.008
47k,"R2,R19,R21,R22,R24,R25,R27",Resistor_SMD:R_0402_1005Metric,7,0.002
2.2,"R7,R8,R11,R12,R15,R16",Resistor_SMD:R_0402_1005Metric,6,0.002
EPC2302,"Q1,Q2,Q3,Q4,Q5,Q6",DronSwarm:EPC2302_QFN-3x5mm,6,4.0
100n,"C15,C23,C31",Capacitor_SMD:C_0603_1608Metric,3,0.008
100n/100V,"C19,C27,C35",Capacitor_SMD:C_0603_1608Metric,3,0.008
1n,"C36,C37,C38",Capacitor_SMD:C_0402_1005Metric,3,0.004
2.7k,"R20,R23,R26",Resistor_SMD:R_0402_1005Metric,3,0.002
Conn_01x01,"J_A,J_B,J_C",DronSwarm:Pad_Power_6x4mm,3,0.0
LMG1210,"U3,U4,U5",DronSwarm:TI_WQFN-19_RVR0019A_4x3mm,3,3.0
10,"R32,R33",Resistor_SMD:R_0402_1005Metric,2,0.002
100,"R36,R37",Resistor_SMD:R_0402_1005Metric,2,0.002
1k,"R34,R44",Resistor_SMD:R_0402_1005Metric,2,0.002
22u/25V,"C6,C7",Capacitor_SMD:C_1210_3225Metric,2,0.12
3.3n,"C8,C39",Capacitor_SMD:C_0402_1005Metric,2,0.004
470u/63V,"C1,C2",Capacitor_THT:CP_Radial_D10.0mm_P5.00mm,2,0.35
Conn_01x01,"J_BATN,J_BATP",DronSwarm:Pad_Power_8x5mm,2,0.0
TPD1E05U06DPY,"U7,U8",Package_SON:Texas_DPY0002A_0.6x1mm_P0.65mm,2,0.08
0.5m/3W,R31,Resistor_SMD:R_Shunt_Vishay_WSK2512_6332Metric_T1.19mm,1,0.35
100k,R3,Resistor_SMD:R_0402_1005Metric,1,0.002
100k,R29,Resistor_SMD:R_0603_1608Metric,1,0.003
10k B3950,TH1,Resistor_SMD:R_0402_1005Metric,1,0.03
1M,R1,Resistor_SMD:R_0603_1608Metric,1,0.003
2.2n/50V,C5,Capacitor_SMD:C_0402_1005Metric,1,0.004
4.7u,C46,Capacitor_SMD:C_0603_1608Metric,1,0.008
453k,R4,Resistor_SMD:R_0402_1005Metric,1,0.002
453k,R6,Resistor_SMD:R_0603_1608Metric,1,0.003
49.9k,R5,Resistor_SMD:R_0402_1005Metric,1,0.002
5.1k,R30,Resistor_SMD:R_0402_1005Metric,1,0.002
56p/C0G,C9,Capacitor_SMD:C_0402_1005Metric,1,0.004
68u,L1,Inductor_SMD:L_Coilcraft_MSS1246-XXX,1,0.45
910,R28,Resistor_SMD:R_0402_1005Metric,1,0.002
Conn_01x03,J_SIG,Connector_JST:JST_GH_SM03B-GHS-TB_1x03-1MP_P1.25mm_Horizontal,1,0.18
Conn_01x05,J4,Connector_PinHeader_1.27mm:PinHeader_1x05_P1.27mm_Vertical,1,0.05
INA181A3,U6,Package_TO_SOT_SMD:SOT-23-6,1,0.35
LM5164DDA,U1,Package_SO:HSOP-8-1EP_3.9x4.9mm_P1.27mm_EP2.41x3.1mm_ThermalVias,1,1.4
MCP1703Ax-330xxTT,U2,Package_TO_SOT_SMD:SOT-23,1,0.35
SMAJ58A,D1,Diode_SMD:D_SMA,1,0.08
STM32G071KBUxN,U9,Package_DFN_QFN:QFN-32-1EP_5x5mm_P0.5mm_EP3.45x3.45mm,1,1.6
TestPoint,TP1,TestPoint:TestPoint_Pad_D1.0mm,1,0.0
verde,D2,LED_SMD:LED_0603_1608Metric,1,0.02
